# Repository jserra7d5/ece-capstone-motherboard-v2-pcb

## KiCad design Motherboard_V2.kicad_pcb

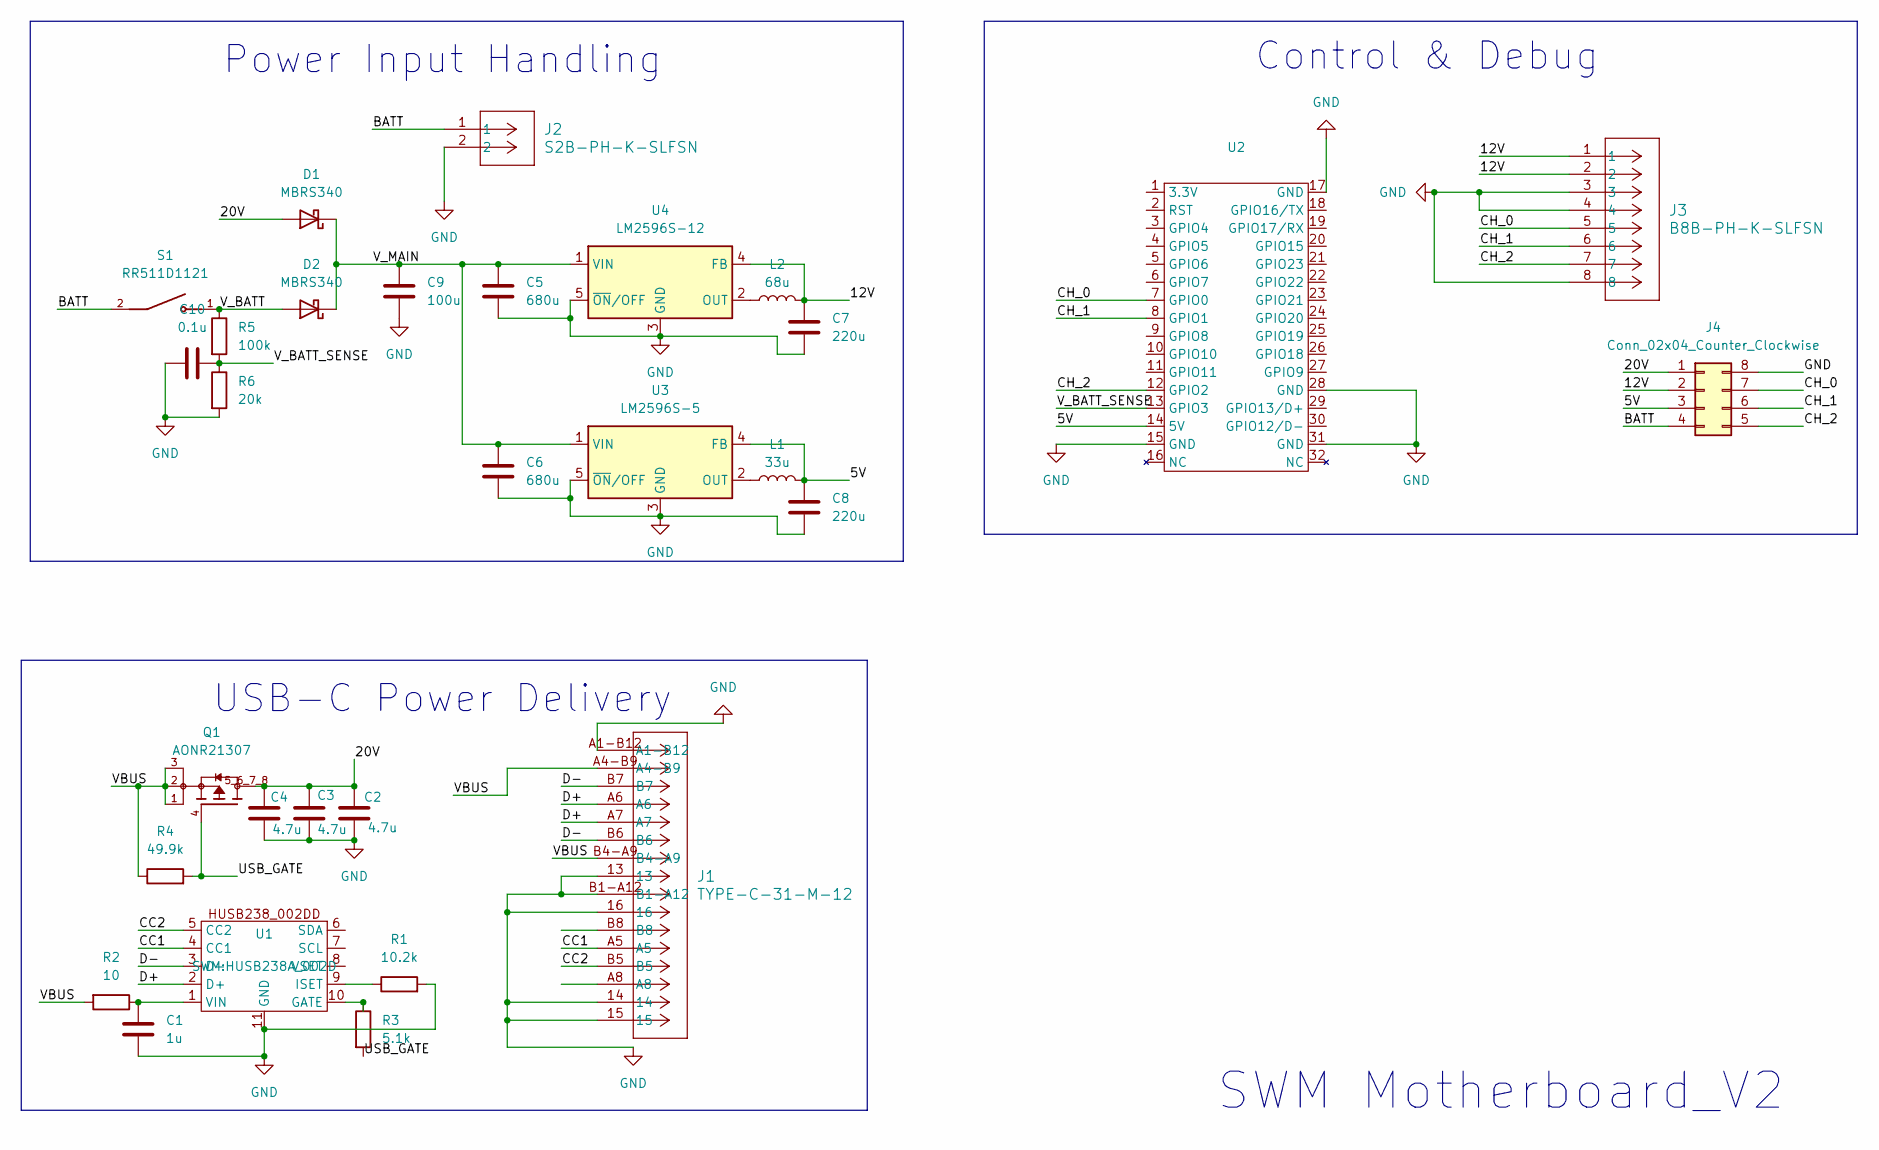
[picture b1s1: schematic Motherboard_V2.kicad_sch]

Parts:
C1: 1u; C_0603_1608Metric_Pad1.08x0.95mm_HandSolder
C2, C3, C4: 4.7u; C_0603_1608Metric_Pad1.08x0.95mm_HandSolder
C5, C6: 680u; C_0603_1608Metric_Pad1.08x0.95mm_HandSolder
C7, C8: 220u; C_0603_1608Metric_Pad1.08x0.95mm_HandSolder
C9: 100u; C_0603_1608Metric_Pad1.08x0.95mm_HandSolder
C10: 0.1u; C_0603_1608Metric_Pad1.08x0.95mm_HandSolder
D1, D2: MBRS340; D_SMC
J1: TYPE-C-31-M-12; CONN12_C-31-M-12_HRO
J2: S2B-PH-K-SLFSN; CONN_S2B-PH-K-S_JST
J3: B8B-PH-K-SLFSN; CONN_B8B-PH-K-S_JST
J4: Conn_02x04_Counter_Clockwise; PinHeader_2x04_P2.54mm_Vertical
L1: 33u; IND_BOURNS_SRN6045
L2: 68u; IND_BOURNS_SRR1210
Q1: AONR21307; TRANS_AONR21307; PARTREV 1.1
R1: 10.2k; R_0603_1608Metric_Pad0.98x0.95mm_HandSolder
R2: 10; R_0603_1608Metric_Pad0.98x0.95mm_HandSolder
R3: 5.1k; R_0603_1608Metric_Pad0.98x0.95mm_HandSolder
R4: 49.9k; R_0603_1608Metric_Pad0.98x0.95mm_HandSolder
R5: 100k; R_0603_1608Metric_Pad0.98x0.95mm_HandSolder
R6: 20k; R_0603_1608Metric_Pad0.98x0.95mm_HandSolder
S1: RR511D1121; E-SWITCH_RR511D1121; PARTREV A
U1: HUSB238A_002D
U2: E
U3: LM2596S-5; TO-263-5_TabPin3
U4: LM2596S-12; TO-263-5_TabPin3

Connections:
/5V: C8.1, J4.3, L1.2, U2.14 (5V), U3.4 (FB)
/12V: C7.1, J3.1, J3.2, J4.2, L2.2, U4.4 (FB)
/20V: C2.1, C3.1, C4.1, D1.2 (A), J4.1, Q1.5_6_7_8
/BATT: J2.1, J4.4, S1.2
/CC1: J1.A5, U1.4 (CC1)
/CC2: J1.B5, U1.5 (CC2)
/CH_0: J3.5, J4.7, U2.7 (GPIO0)
/CH_1: J3.6, J4.6, U2.8 (GPIO1)
/CH_2: J3.7, J4.5, U2.12 (GPIO2)
/D+: J1.A6, J1.A7, U1.2 (D+)
/D-: J1.B6, J1.B7, U1.3 (D-)
/USB_GATE: Q1.4, R3.2, R4.2
/VBUS: J1.A4-B9, J1.B4-A9, Q1.1, Q1.2, Q1.3, R2.2, R4.1
/V_BATT: D2.2 (A), R5.1, S1.1
/V_BATT_SENSE: C10.2, R5.2, R6.1, U2.13 (GPIO3)
/V_MAIN: C5.1, C6.1, C9.1, D1.1 (K), D2.1 (K), U3.1 (VIN), U4.1 (VIN)
GND: C1.2, C2.2, C3.2, C4.2, C5.2, C6.2, C7.2, C8.2, C9.2, C10.1, J1.13, J1.14, J1.15, J1.16, J1.A1-B12, J1.B1-A12, J2.2, J3.3, J3.4, J3.8, J4.8, R1.2, R6.2, U1.11 (GND), U2.15 (GND), U2.17 (GND), U2.28 (GND), U2.31 (GND), U3.3 (GND), U3.5 (~ON/OFF), U4.3 (GND), U4.5 (~ON/OFF)
unnamed: R3.1, U1.10 (GATE)
unnamed: R1.1, U1.9 (ISET)
unnamed: C1.1, R2.1, U1.1 (VIN)
unnamed: L1.1, U3.2 (OUT)
unnamed: L2.1, U4.2 (OUT)

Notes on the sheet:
Power Input Handling
Control & Debug
USB-C Power Delivery
SWM Motherboard_V2

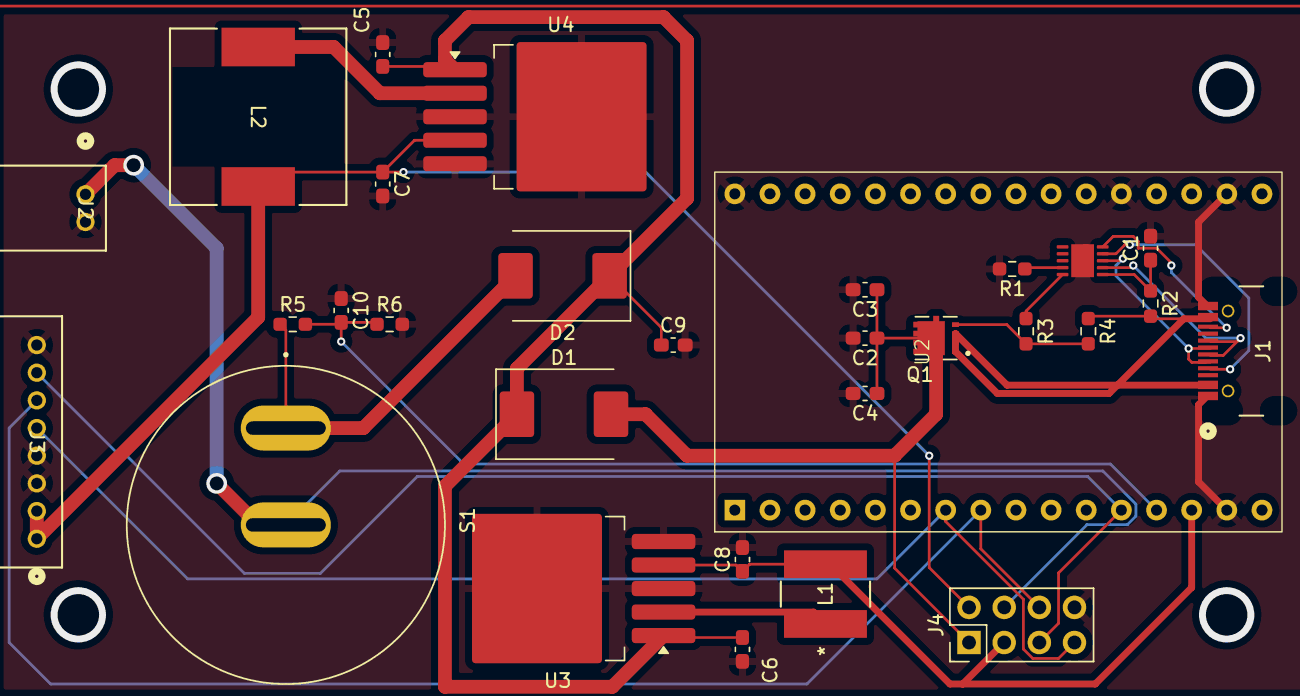
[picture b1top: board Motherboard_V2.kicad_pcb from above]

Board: 2 copper layers, 30 parts (0 on the bottom side), 22 nets.
